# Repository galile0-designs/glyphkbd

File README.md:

# glyphkbd
**5x13 ortholinear plus TKL nav and arrow clusters**  - Key layout inspired by [drFaustroll's m65](https://mlego.elena.space/m65/) as well as [Stucco](https://www.reddit.com/r/CustomKeyboards/comments/10k8k6w/custom_ortho_tkl_done_stucco1510/).

# v2
glyphkbd_v2 uses a custom PCB with integrated STM32F072 microcontroller using [QMK firmware](https://github.com/qmk/qmk_firmware) [(here)](https://github.com/qmk/qmk_firmware/pull/23131), with [VIA](https://github.com/the-via) use enabled. 3D printed top mount case, [UDB](https://github.com/Unified-Daughterboard/Unified-Daughterboard.github.io) daughterboard for external USB-C connection.

# License
glyphkbd is licensed under Creative Commons Attribution-NonCommercial-ShareAlike 4.0

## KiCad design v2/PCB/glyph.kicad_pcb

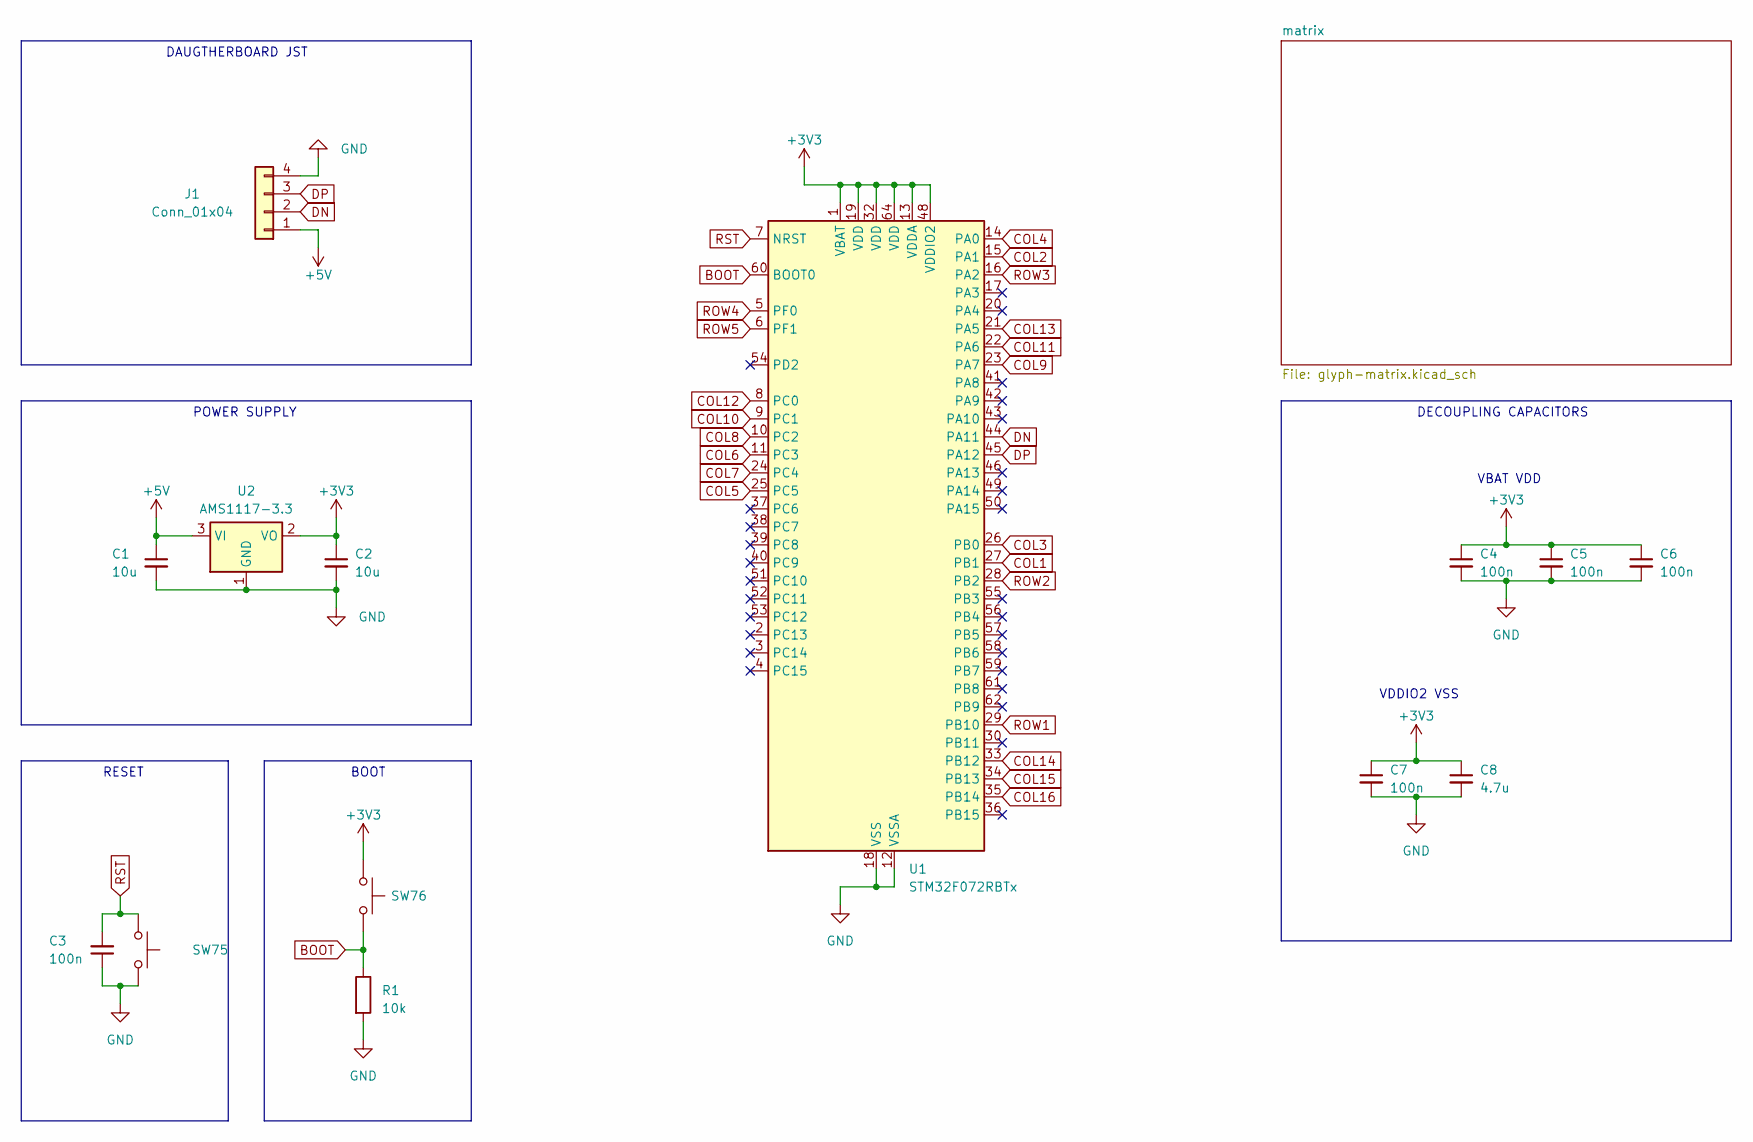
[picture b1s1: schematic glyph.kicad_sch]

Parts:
C1, C2: 10u; C_0402_1005Metric; LCSC C15525
C3, C4, C5, C6, C7: 100n; C_0402_1005Metric; LCSC C1525
C8: 4.7u; C_0402_1005Metric; LCSC C23733
J1: Conn_01x04; UDB_labeled_JST_SH_SM04B-SRSS-TB_1x04-1MP_P1.00mm_Horizontal; LCSC C160404
R1: 10k; R_0603_1608Metric; LCSC C25804
SW75, SW76: SW_Push; SW_Push_1P1T_XKB_TS-1187A; LCSC C318884
U1: STM32F072RBTx; LQFP-64_10x10mm_P0.5mm; LCSC C46046
U2: AMS1117-3.3; SOT-223-3_TabPin2; LCSC C6186

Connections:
+3V3: C2.1, C4.1, C5.1, C6.1, C7.1, C8.1, SW76.1, U1.1 (VBAT), U1.13 (VDDA), U1.19 (VDD), U1.32 (VDD), U1.48 (VDDIO2), U1.64 (VDD), U2.2 (VO); also elsewhere on the board
+5V: C1.1, J1.1, U2.3 (VI)
BOOT: R1.1, SW76.2, U1.60 (BOOT0); also elsewhere on the board
COL1: U1.27 (PB1); also elsewhere on the board
COL2: U1.15 (PA1); also elsewhere on the board
COL3: U1.26 (PB0); also elsewhere on the board
COL4: U1.14 (PA0); also elsewhere on the board
COL5: U1.25 (PC5); also elsewhere on the board
COL6: U1.11 (PC3); also elsewhere on the board
COL7: U1.24 (PC4); also elsewhere on the board
COL8: U1.10 (PC2); also elsewhere on the board
COL9: U1.23 (PA7); also elsewhere on the board
COL10: U1.9 (PC1); also elsewhere on the board
COL11: U1.22 (PA6); also elsewhere on the board
COL12: U1.8 (PC0); also elsewhere on the board
COL13: U1.21 (PA5); also elsewhere on the board
COL14: U1.33 (PB12); also elsewhere on the board
COL15: U1.34 (PB13); also elsewhere on the board
COL16: U1.35 (PB14); also elsewhere on the board
DN: J1.2, U1.44 (PA11)
DP: J1.3, U1.45 (PA12)
GND: C1.2, C2.2, C3.1, C4.2, C5.2, C6.2, C7.2, C8.2, J1.4, J1.MP, R1.2, SW75.1, U1.12 (VSSA), U1.18 (VSS), U1.31 (VSS), U1.47 (VSS), U1.63 (VSS), U2.1 (GND); also elsewhere on the board
ROW1: U1.29 (PB10); also elsewhere on the board
ROW2: U1.28 (PB2); also elsewhere on the board
ROW3: U1.16 (PA2); also elsewhere on the board
ROW4: U1.5 (PF0); also elsewhere on the board
ROW5: U1.6 (PF1); also elsewhere on the board
RST: C3.2, SW75.2, U1.7 (NRST); also elsewhere on the board

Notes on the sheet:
DAUGTHERBOARD JST
BOOT
VBAT VDD
RESET
DECOUPLING CAPACITORS
POWER SUPPLY
VDDIO2 VSS

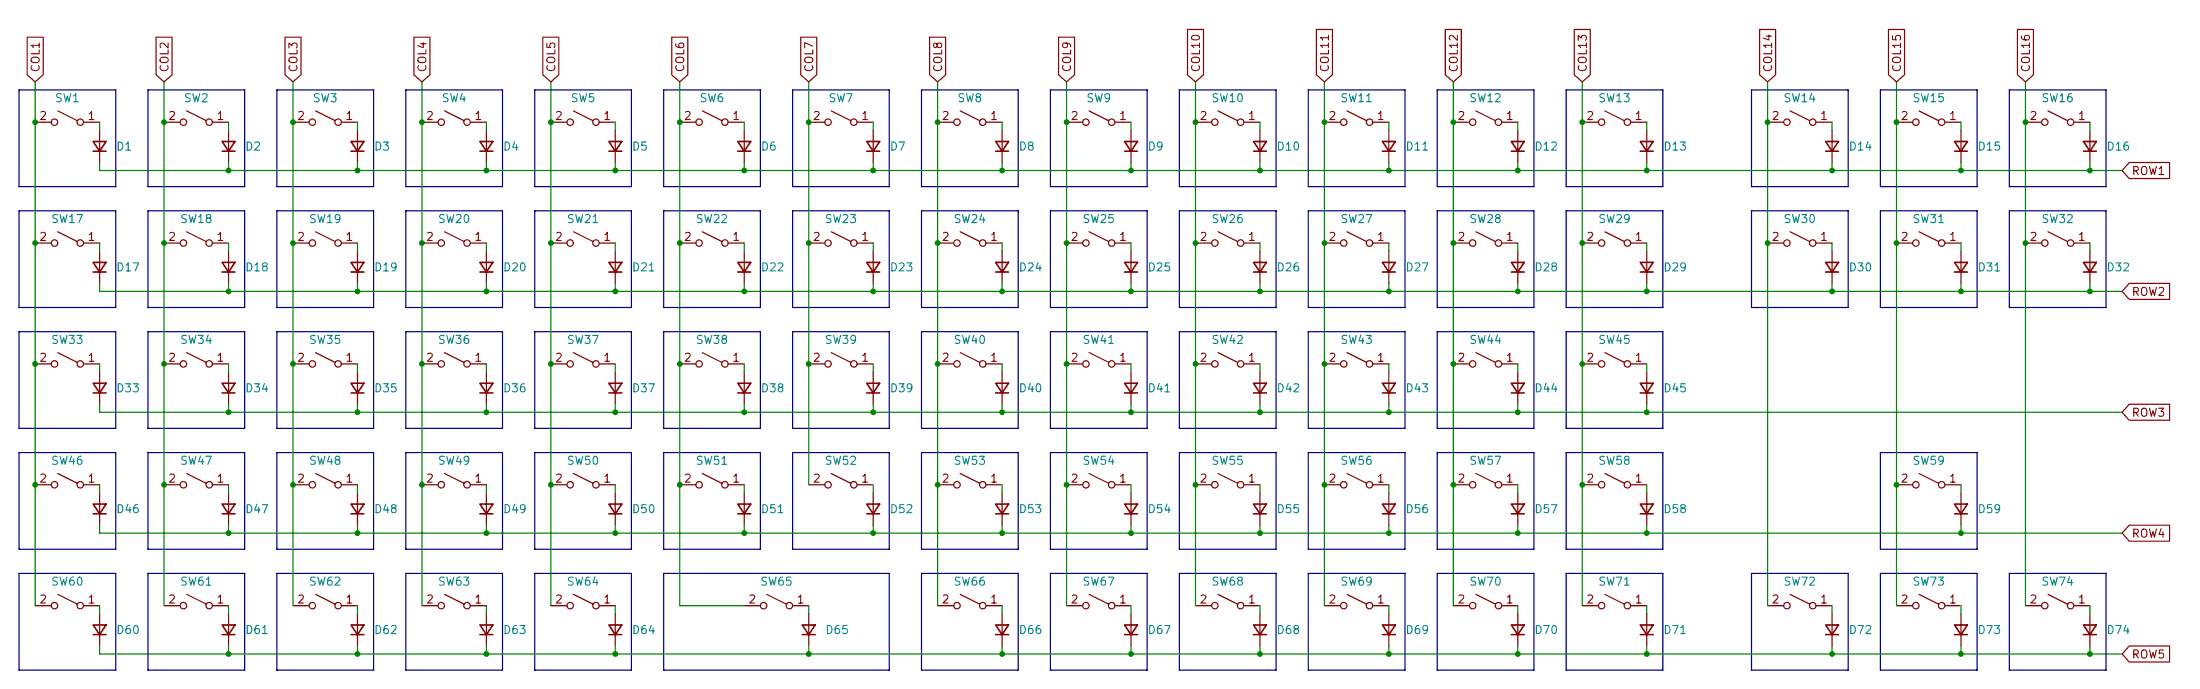
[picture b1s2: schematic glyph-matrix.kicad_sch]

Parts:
D1, D2, D3, D4, D5, D6, D7, D8, D9, D10, D11, D12, D13, D14, D15, D16, D17, D18, D19, D20, D21, D22, D23, D24, D25, D26, D27, D28, D29, D30, D31, D32, D33, D34, D35, D36, D37, D38, D39, D40, D41, D42, D43, D44, D45, D46, D47, D48, D49, D50, D51, D52, D53, D54, D55, D56, D57, D58, D59, D60, D61, D62, D63, D64, D65, D66, D67, D68, D69, D70, D71, D72, D73, D74: D; D_SOD-123; LCSC C81598
SW1, SW2, SW3, SW4, SW5, SW6, SW7, SW8, SW9, SW10, SW11, SW12, SW13, SW14, SW15, SW16, SW17, SW18, SW19, SW20, SW21, SW22, SW23, SW24, SW25, SW26, SW27, SW28, SW29, SW30, SW31, SW32, SW33, SW34, SW35, SW36, SW37, SW38, SW39, SW40, SW41, SW42, SW43, SW44, SW45, SW46, SW47, SW48, SW49, SW50, SW51, SW52, SW53, SW54, SW55, SW56, SW57, SW58, SW59, SW60, SW61, SW62, SW63, SW64, SW66, SW67, SW68, SW69, SW70, SW71, SW72, SW73, SW74: SW_SPST; CherryMX_Hotswap-Solderable_1u; LCSC C5156480
SW65: SW_SPST; CherryMX_Hotswap-Solderable_2u; LCSC C5156480

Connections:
COL1: SW1.2 (B), SW17.2 (B), SW33.2 (B), SW46.2 (B), SW60.2 (B); also elsewhere on the board
COL2: SW2.2 (B), SW18.2 (B), SW34.2 (B), SW47.2 (B), SW61.2 (B); also elsewhere on the board
COL3: SW3.2 (B), SW19.2 (B), SW35.2 (B), SW48.2 (B), SW62.2 (B); also elsewhere on the board
COL4: SW4.2 (B), SW20.2 (B), SW36.2 (B), SW49.2 (B), SW63.2 (B); also elsewhere on the board
COL5: SW5.2 (B), SW21.2 (B), SW37.2 (B), SW50.2 (B), SW64.2 (B); also elsewhere on the board
COL6: SW6.2 (B), SW22.2 (B), SW38.2 (B), SW51.2 (B), SW65.2 (B); also elsewhere on the board
COL7: SW7.2 (B), SW23.2 (B), SW39.2 (B), SW52.2 (B); also elsewhere on the board
COL8: SW8.2 (B), SW24.2 (B), SW40.2 (B), SW53.2 (B), SW66.2 (B); also elsewhere on the board
COL9: SW9.2 (B), SW25.2 (B), SW41.2 (B), SW54.2 (B), SW67.2 (B); also elsewhere on the board
COL10: SW10.2 (B), SW26.2 (B), SW42.2 (B), SW55.2 (B), SW68.2 (B); also elsewhere on the board
COL11: SW11.2 (B), SW27.2 (B), SW43.2 (B), SW56.2 (B), SW69.2 (B); also elsewhere on the board
COL12: SW12.2 (B), SW28.2 (B), SW44.2 (B), SW57.2 (B), SW70.2 (B); also elsewhere on the board
COL13: SW13.2 (B), SW29.2 (B), SW45.2 (B), SW58.2 (B), SW71.2 (B); also elsewhere on the board
COL14: SW14.2 (B), SW30.2 (B), SW72.2 (B); also elsewhere on the board
COL15: SW15.2 (B), SW31.2 (B), SW59.2 (B), SW73.2 (B); also elsewhere on the board
COL16: SW16.2 (B), SW32.2 (B), SW74.2 (B); also elsewhere on the board
unnamed: D1.2 (A), SW1.1 (A)
unnamed: D2.2 (A), SW2.1 (A)
unnamed: D3.2 (A), SW3.1 (A)
unnamed: D4.2 (A), SW4.1 (A)
unnamed: D5.2 (A), SW5.1 (A)
unnamed: D6.2 (A), SW6.1 (A)
unnamed: D7.2 (A), SW7.1 (A)
unnamed: D8.2 (A), SW8.1 (A)
unnamed: D9.2 (A), SW9.1 (A)
unnamed: D10.2 (A), SW10.1 (A)
unnamed: D11.2 (A), SW11.1 (A)
unnamed: D12.2 (A), SW12.1 (A)
unnamed: D13.2 (A), SW13.1 (A)
unnamed: D14.2 (A), SW14.1 (A)
unnamed: D15.2 (A), SW15.1 (A)
unnamed: D16.2 (A), SW16.1 (A)
unnamed: D17.2 (A), SW17.1 (A)
unnamed: D18.2 (A), SW18.1 (A)
unnamed: D19.2 (A), SW19.1 (A)
unnamed: D20.2 (A), SW20.1 (A)
unnamed: D21.2 (A), SW21.1 (A)
unnamed: D22.2 (A), SW22.1 (A)
unnamed: D23.2 (A), SW23.1 (A)
unnamed: D24.2 (A), SW24.1 (A)
unnamed: D25.2 (A), SW25.1 (A)
unnamed: D26.2 (A), SW26.1 (A)
unnamed: D27.2 (A), SW27.1 (A)
unnamed: D28.2 (A), SW28.1 (A)
unnamed: D29.2 (A), SW29.1 (A)
unnamed: D30.2 (A), SW30.1 (A)
unnamed: D31.2 (A), SW31.1 (A)
unnamed: D32.2 (A), SW32.1 (A)
unnamed: D33.2 (A), SW33.1 (A)
unnamed: D34.2 (A), SW34.1 (A)
unnamed: D35.2 (A), SW35.1 (A)
unnamed: D36.2 (A), SW36.1 (A)
unnamed: D37.2 (A), SW37.1 (A)
unnamed: D38.2 (A), SW38.1 (A)
unnamed: D39.2 (A), SW39.1 (A)
unnamed: D40.2 (A), SW40.1 (A)
unnamed: D41.2 (A), SW41.1 (A)
unnamed: D42.2 (A), SW42.1 (A)
unnamed: D43.2 (A), SW43.1 (A)
unnamed: D44.2 (A), SW44.1 (A)
unnamed: D45.2 (A), SW45.1 (A)
unnamed: D46.2 (A), SW46.1 (A)
unnamed: D47.2 (A), SW47.1 (A)
unnamed: D48.2 (A), SW48.1 (A)
unnamed: D49.2 (A), SW49.1 (A)
unnamed: D50.2 (A), SW50.1 (A)
unnamed: D51.2 (A), SW51.1 (A)
unnamed: D52.2 (A), SW52.1 (A)
unnamed: D53.2 (A), SW53.1 (A)
unnamed: D54.2 (A), SW54.1 (A)
unnamed: D55.2 (A), SW55.1 (A)
unnamed: D56.2 (A), SW56.1 (A)
unnamed: D57.2 (A), SW57.1 (A)
unnamed: D58.2 (A), SW58.1 (A)
unnamed: D59.2 (A), SW59.1 (A)
unnamed: D60.2 (A), SW60.1 (A)
unnamed: D61.2 (A), SW61.1 (A)
unnamed: D62.2 (A), SW62.1 (A)
unnamed: D63.2 (A), SW63.1 (A)
unnamed: D64.2 (A), SW64.1 (A)
unnamed: D65.2 (A), SW65.1 (A)
unnamed: D66.2 (A), SW66.1 (A)
unnamed: D67.2 (A), SW67.1 (A)
unnamed: D68.2 (A), SW68.1 (A)
unnamed: D69.2 (A), SW69.1 (A)
unnamed: D70.2 (A), SW70.1 (A)
unnamed: D71.2 (A), SW71.1 (A)
unnamed: D72.2 (A), SW72.1 (A)
unnamed: D73.2 (A), SW73.1 (A)
unnamed: D74.2 (A), SW74.1 (A)
ROW1: D1.1 (K), D2.1 (K), D3.1 (K), D4.1 (K), D5.1 (K), D6.1 (K), D7.1 (K), D8.1 (K), D9.1 (K), D10.1 (K), D11.1 (K), D12.1 (K), D13.1 (K), D14.1 (K), D15.1 (K), D16.1 (K); also elsewhere on the board
ROW2: D17.1 (K), D18.1 (K), D19.1 (K), D20.1 (K), D21.1 (K), D22.1 (K), D23.1 (K), D24.1 (K), D25.1 (K), D26.1 (K), D27.1 (K), D28.1 (K), D29.1 (K), D30.1 (K), D31.1 (K), D32.1 (K); also elsewhere on the board
ROW3: D33.1 (K), D34.1 (K), D35.1 (K), D36.1 (K), D37.1 (K), D38.1 (K), D39.1 (K), D40.1 (K), D41.1 (K), D42.1 (K), D43.1 (K), D44.1 (K), D45.1 (K); also elsewhere on the board
ROW4: D46.1 (K), D47.1 (K), D48.1 (K), D49.1 (K), D50.1 (K), D51.1 (K), D52.1 (K), D53.1 (K), D54.1 (K), D55.1 (K), D56.1 (K), D57.1 (K), D58.1 (K), D59.1 (K); also elsewhere on the board
ROW5: D60.1 (K), D61.1 (K), D62.1 (K), D63.1 (K), D64.1 (K), D65.1 (K), D66.1 (K), D67.1 (K), D68.1 (K), D69.1 (K), D70.1 (K), D71.1 (K), D72.1 (K), D73.1 (K), D74.1 (K); also elsewhere on the board

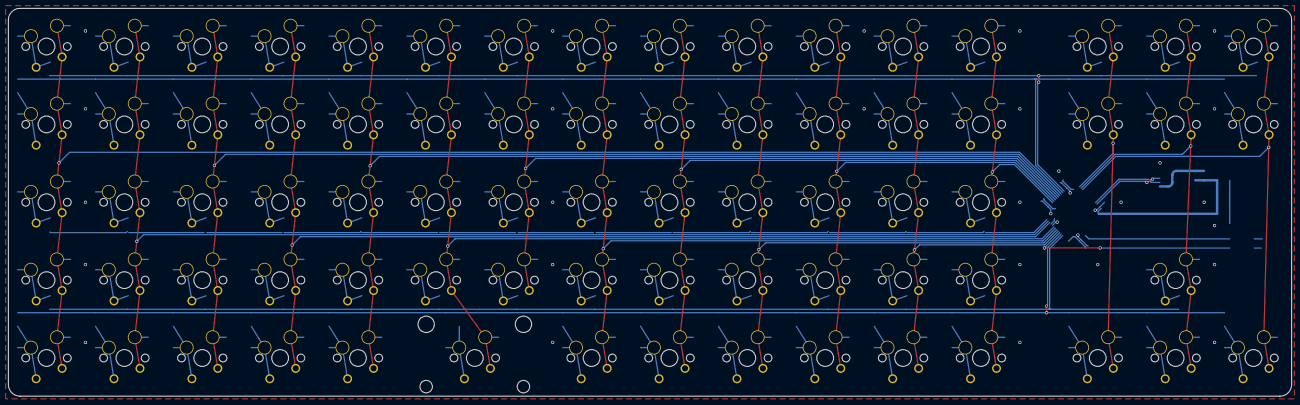
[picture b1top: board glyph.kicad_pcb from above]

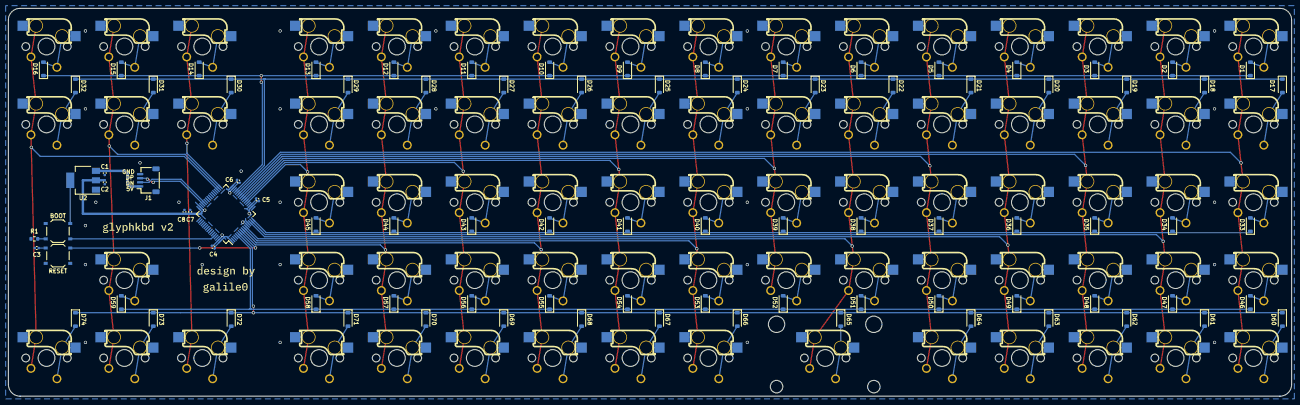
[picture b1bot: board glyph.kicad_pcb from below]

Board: 2 copper layers, 313.9 x 94.9 mm, 162 parts (162 on the bottom side), 102 nets.

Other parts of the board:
BOOT: SW_Push; SW_Push_1P1T_XKB_TS-1187A
RESET: SW_Push; SW_Push_1P1T_XKB_TS-1187A

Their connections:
+3V3: BOOT.1; also elsewhere on the board
BOOT: BOOT.2; also elsewhere on the board
GND: RESET.1; also elsewhere on the board
RST: RESET.2; also elsewhere on the board

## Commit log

2023-11-16 Create LICENSE
2023-11-18 v1.2 upload
2023-11-18 kle json upload
2023-11-18 retract v1.2 firmware
2023-11-18 firmware update
2023-11-20 verification file
2024-02-22 Update LICENSE
2024-03-09 add v2 qmk/via support
2024-03-09 added v2 pcb files
2024-08-07 publish case and plate files
